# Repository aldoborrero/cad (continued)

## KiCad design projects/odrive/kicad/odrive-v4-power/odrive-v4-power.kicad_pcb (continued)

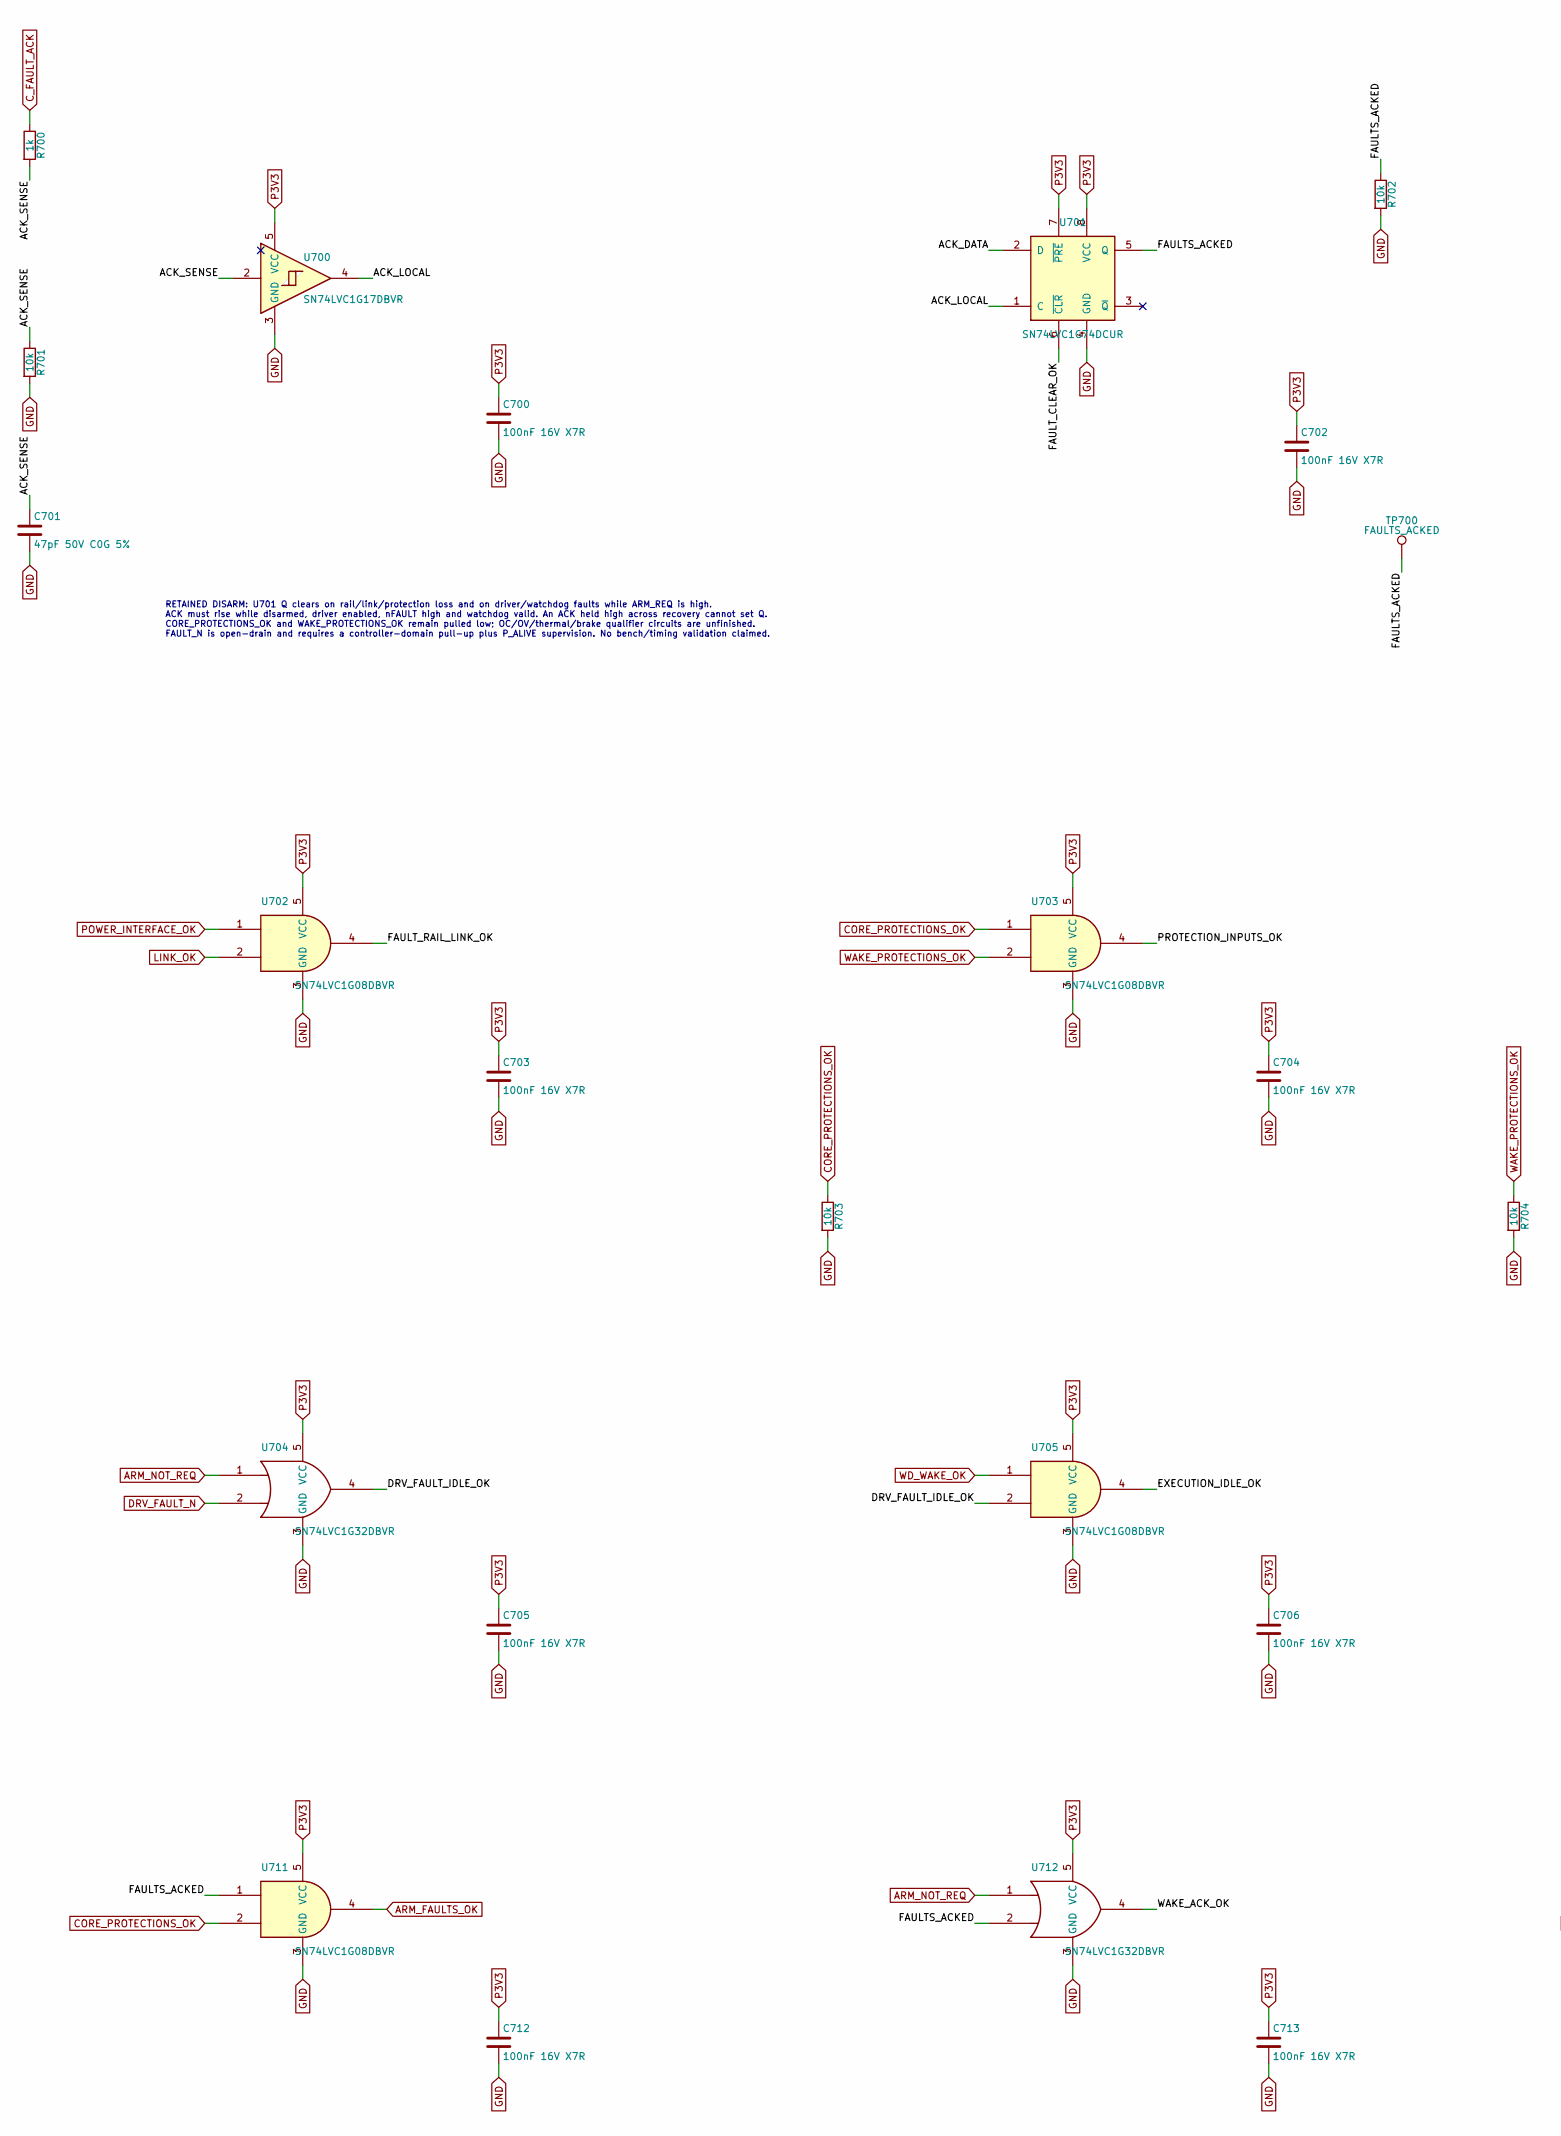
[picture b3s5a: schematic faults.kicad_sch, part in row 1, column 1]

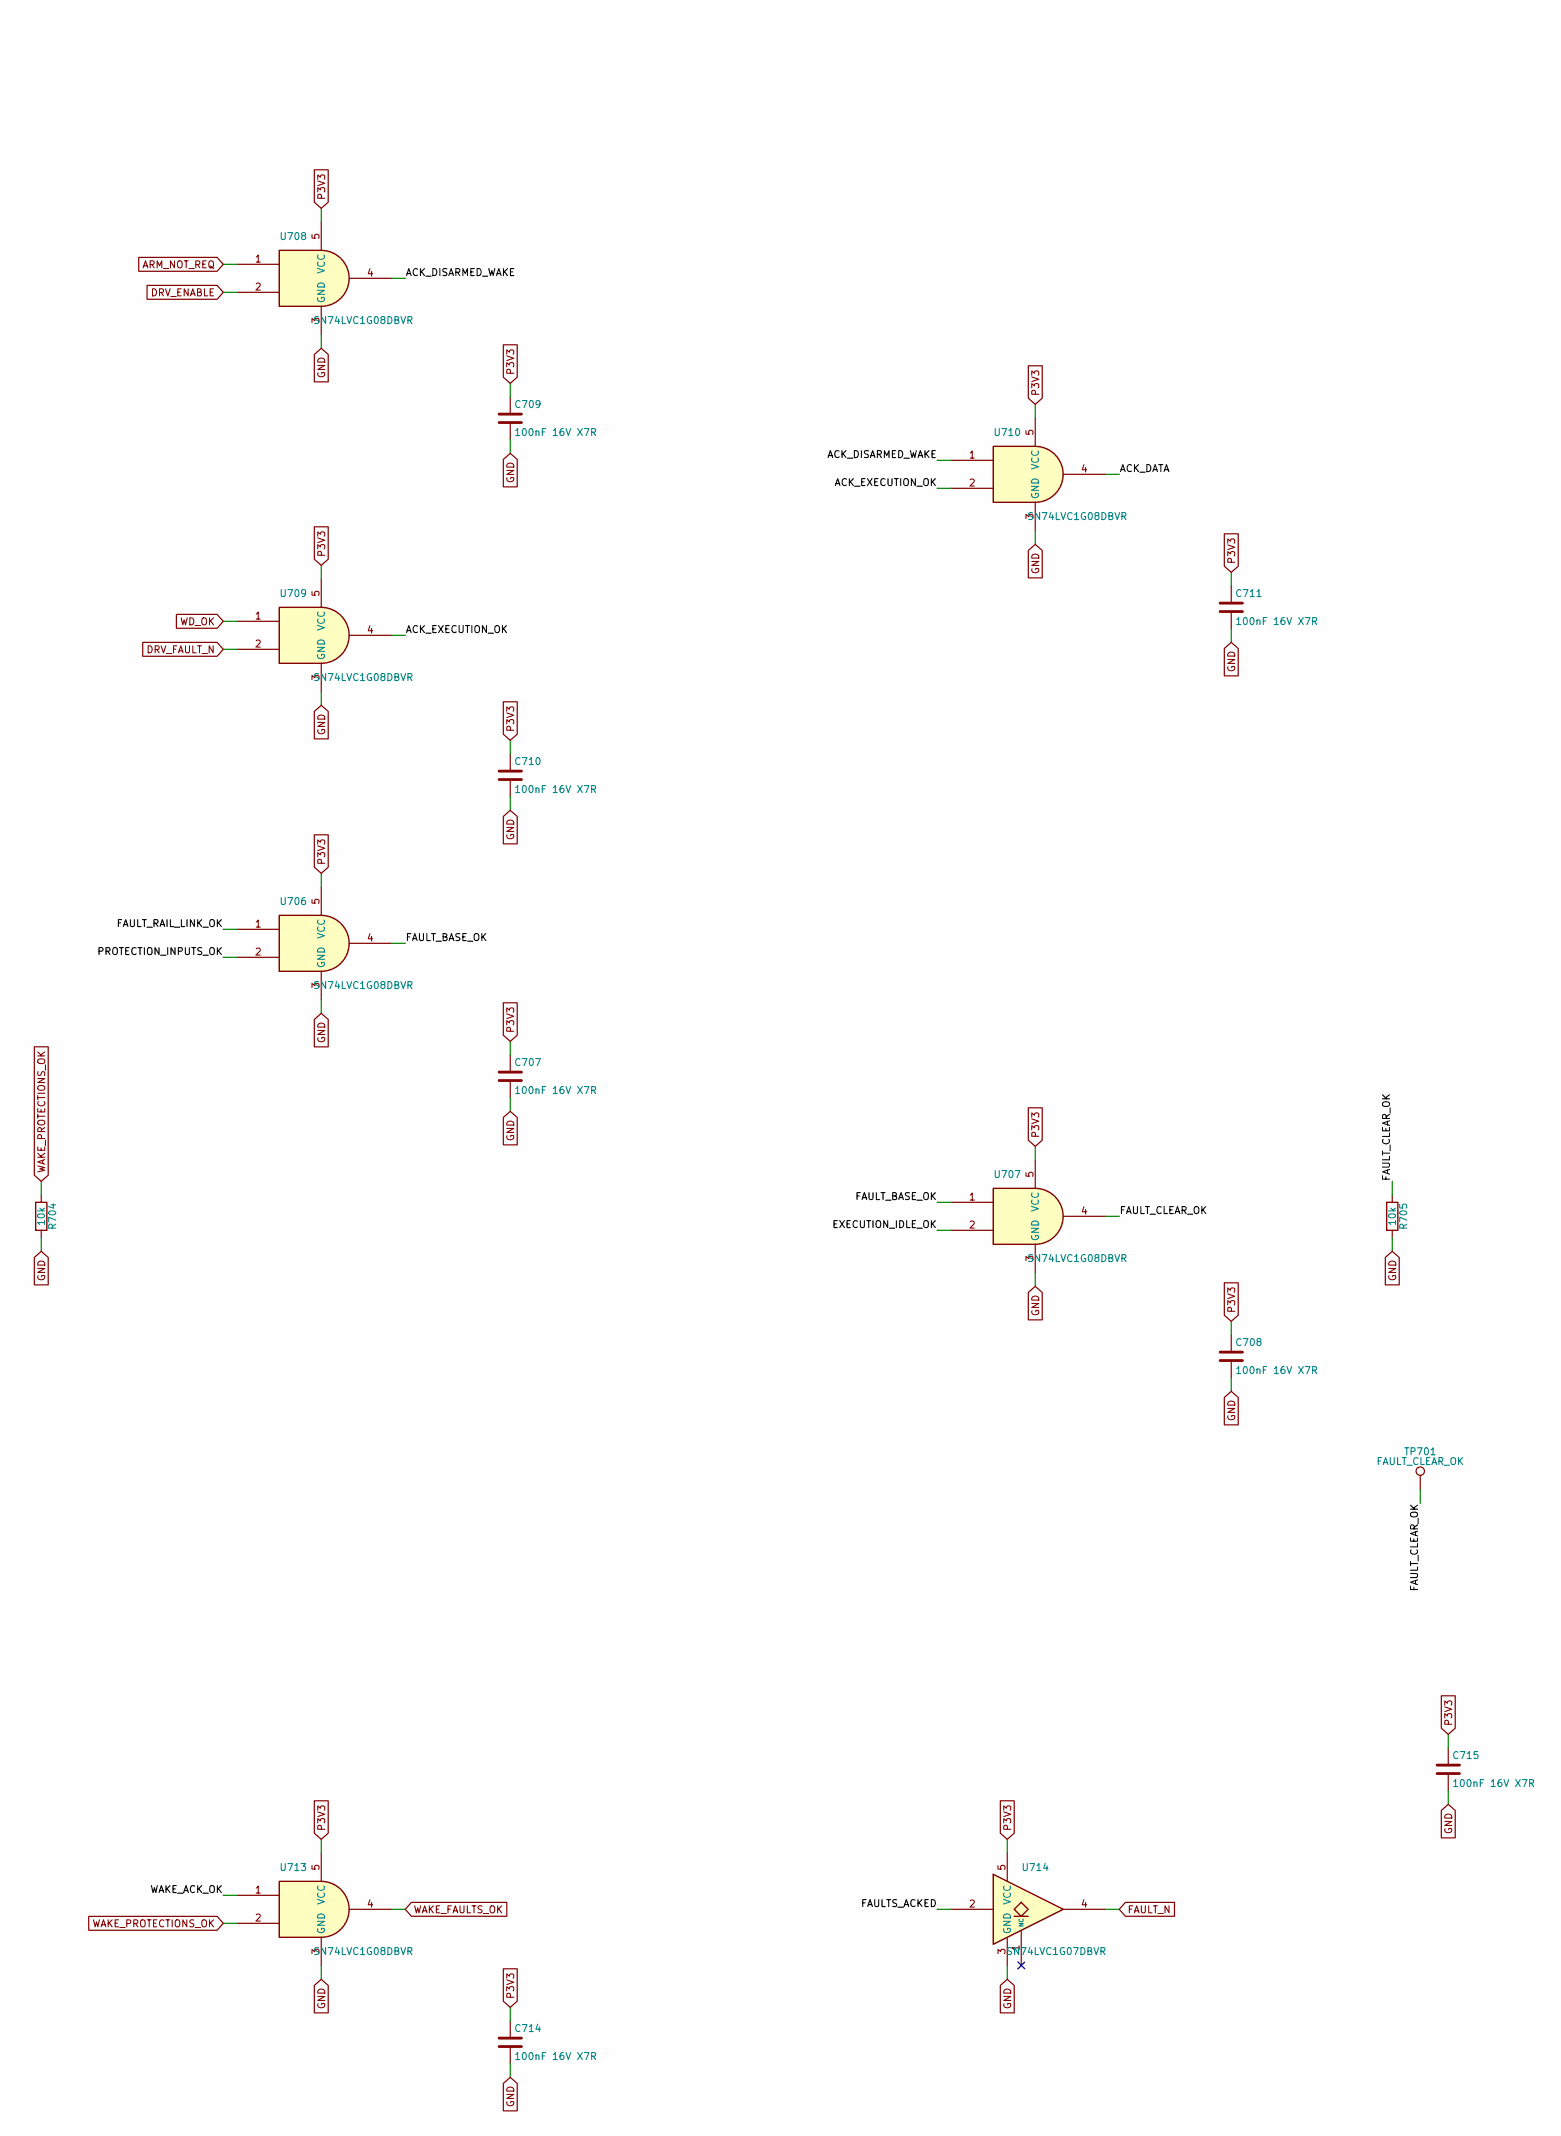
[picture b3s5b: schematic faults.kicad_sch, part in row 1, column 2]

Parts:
C700, C702, C703, C704, C705, C706, C707, C708, C709, C710, C711, C712, C713, C714, C715: 100nF 16V X7R; C_0603_1608Metric
C701: 47pF 50V C0G 5%; C_0603_1608Metric
R700: 1k; R_0603_1608Metric
R701, R702, R703, R704, R705: 10k; R_0603_1608Metric
TP700: FAULTS_ACKED; TestPoint_Pad_D1.0mm
TP701: FAULT_CLEAR_OK; TestPoint_Pad_D1.0mm
U700: SN74LVC1G17DBVR; SOT-23-5
U701: SN74LVC1G74DCUR; TI_DCU0008A
U702, U703, U705, U706, U707, U708, U709, U710, U711, U713: SN74LVC1G08DBVR; SOT-23-5
U704, U712: SN74LVC1G32DBVR; SOT-23-5
U714: SN74LVC1G07DBVR; SOT-23-5

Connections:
/Retained faults and acknowledgement/ACK_DATA: U701.2 (D), U710.4
/Retained faults and acknowledgement/ACK_DISARMED_WAKE: U708.4, U710.1
/Retained faults and acknowledgement/ACK_EXECUTION_OK: U709.4, U710.2
/Retained faults and acknowledgement/ACK_LOCAL: U700.4, U701.1 (C)
/Retained faults and acknowledgement/ACK_SENSE: C701.1, R700.2, R701.1, U700.2
/Retained faults and acknowledgement/DRV_FAULT_IDLE_OK: U704.4, U705.2
/Retained faults and acknowledgement/EXECUTION_IDLE_OK: U705.4, U707.2
/Retained faults and acknowledgement/FAULTS_ACKED: R702.1, TP700.1, U701.5 (Q), U711.1, U712.2, U714.2
/Retained faults and acknowledgement/FAULT_BASE_OK: U706.4, U707.1
/Retained faults and acknowledgement/FAULT_CLEAR_OK: R705.1, TP701.1, U701.6 (~CLR), U707.4
/Retained faults and acknowledgement/FAULT_RAIL_LINK_OK: U702.4, U706.1
/Retained faults and acknowledgement/PROTECTION_INPUTS_OK: U703.4, U706.2
/Retained faults and acknowledgement/WAKE_ACK_OK: U712.4, U713.1
ARM_FAULTS_OK: U711.4; also elsewhere on the board
ARM_NOT_REQ: U704.1, U708.1, U712.1; also elsewhere on the board
CORE_PROTECTIONS_OK: R703.1, U703.1, U711.2
C_FAULT_ACK: R700.1; also elsewhere on the board
DRV_ENABLE: U708.2; also elsewhere on the board
DRV_FAULT_N: U704.2, U709.2; also elsewhere on the board
FAULT_N: U714.4; also elsewhere on the board
GND: C700.2, C701.2, C702.2, C703.2, C704.2, C705.2, C706.2, C707.2, C708.2, C709.2, C710.2, C711.2, C712.2, C713.2, C714.2, C715.2, R701.2, R702.2, R703.2, R704.2, R705.2, U700.3 (GND), U701.4 (GND), U702.3 (GND), U703.3 (GND), U704.3 (GND), U705.3 (GND), U706.3 (GND), U707.3 (GND), U708.3 (GND), U709.3 (GND), U710.3 (GND), U711.3 (GND), U712.3 (GND), U713.3 (GND), U714.3 (GND); also elsewhere on the board
LINK_OK: U702.2; also elsewhere on the board
P3V3: C700.1, C702.1, C703.1, C704.1, C705.1, C706.1, C707.1, C708.1, C709.1, C710.1, C711.1, C712.1, C713.1, C714.1, C715.1, U700.5 (VCC), U701.7 (~PRE), U701.8 (VCC), U702.5 (VCC), U703.5 (VCC), U704.5 (VCC), U705.5 (VCC), U706.5 (VCC), U707.5 (VCC), U708.5 (VCC), U709.5 (VCC), U710.5 (VCC), U711.5 (VCC), U712.5 (VCC), U713.5 (VCC), U714.5 (VCC); also elsewhere on the board
POWER_INTERFACE_OK: U702.1; also elsewhere on the board
WAKE_FAULTS_OK: U713.4; also elsewhere on the board
WAKE_PROTECTIONS_OK: R704.1, U703.2, U713.2
WD_OK: U709.1; also elsewhere on the board
WD_WAKE_OK: U705.1; also elsewhere on the board

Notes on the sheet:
RETAINED DISARM: U701 Q clears on rail/link/protection loss and on driver/watchdog faults while ARM_REQ is high. ACK must rise while disarmed, driver enabled, nFAULT high and watchdog valid. An ACK held high across recovery cannot set Q. CORE_PROTECTIONS_OK and WAKE_PROTECTIONS_OK remain pulled low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

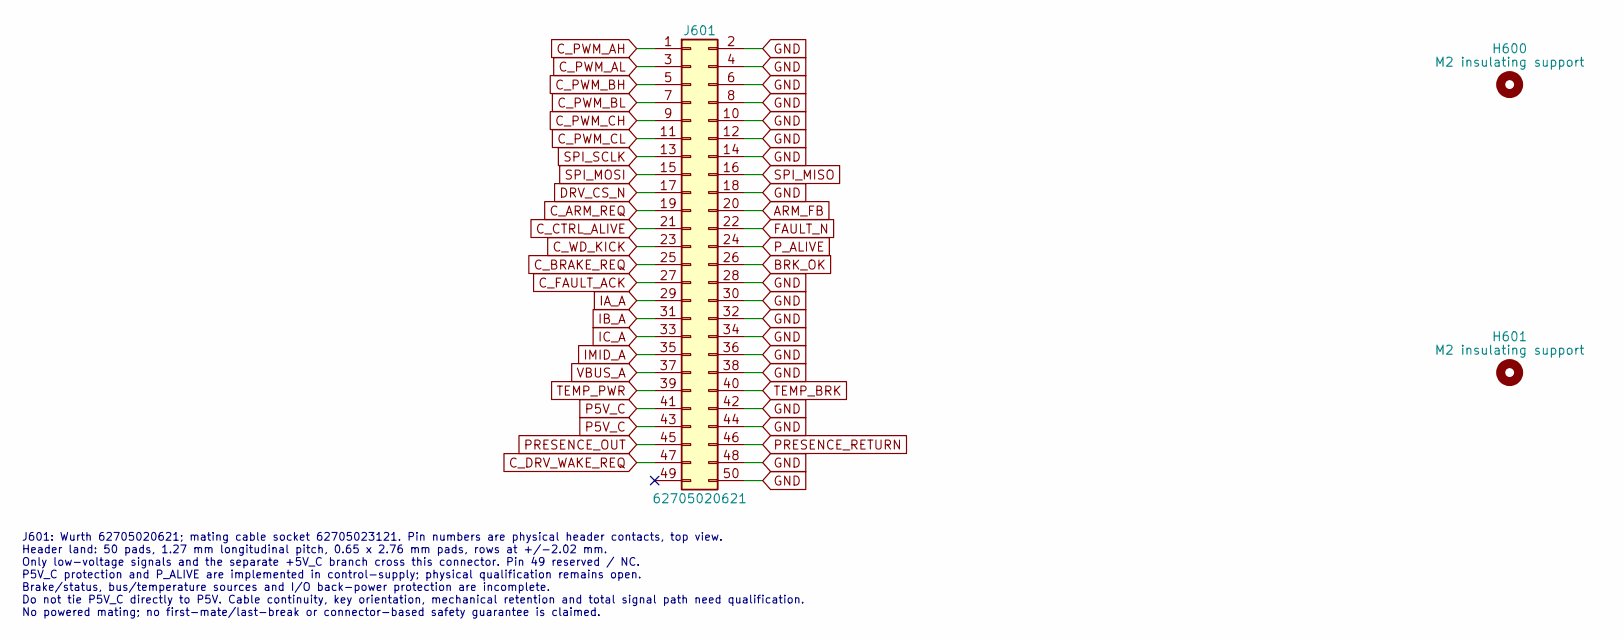
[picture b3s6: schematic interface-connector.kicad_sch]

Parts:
H600, H601: M2 insulating support; MountingHole_2.2mm_M2_Head5mm
J601: 62705020621; Wurth_62705020621_2x25_P1.27mm

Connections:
ARM_FB: J601.20; also elsewhere on the board
BRK_OK: J601.26
C_ARM_REQ: J601.19; also elsewhere on the board
C_BRAKE_REQ: J601.25
C_CTRL_ALIVE: J601.21; also elsewhere on the board
C_DRV_WAKE_REQ: J601.47; also elsewhere on the board
C_FAULT_ACK: J601.27; also elsewhere on the board
C_PWM_AH: J601.1; also elsewhere on the board
C_PWM_AL: J601.3; also elsewhere on the board
C_PWM_BH: J601.5; also elsewhere on the board
C_PWM_BL: J601.7; also elsewhere on the board
C_PWM_CH: J601.9; also elsewhere on the board
C_PWM_CL: J601.11; also elsewhere on the board
C_WD_KICK: J601.23; also elsewhere on the board
DRV_CS_N: J601.17; also elsewhere on the board
FAULT_N: J601.22; also elsewhere on the board
GND: J601.2, J601.4, J601.6, J601.8, J601.10, J601.12, J601.14, J601.18, J601.28, J601.30, J601.32, J601.34, J601.36, J601.38, J601.42, J601.44, J601.48, J601.50; also elsewhere on the board
IA_A: J601.29; also elsewhere on the board
IB_A: J601.31; also elsewhere on the board
IC_A: J601.33; also elsewhere on the board
IMID_A: J601.35; also elsewhere on the board
P5V_C: J601.41, J601.43; also elsewhere on the board
PRESENCE_OUT: J601.45; also elsewhere on the board
PRESENCE_RETURN: J601.46; also elsewhere on the board
P_ALIVE: J601.24; also elsewhere on the board
SPI_MISO: J601.16; also elsewhere on the board
SPI_MOSI: J601.15; also elsewhere on the board
SPI_SCLK: J601.13; also elsewhere on the board
TEMP_BRK: J601.40
TEMP_PWR: J601.39
VBUS_A: J601.37

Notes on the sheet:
J601: Wurth 62705020621; mating cable socket 62705023121. Pin numbers are physical header contacts, top view. Header land: 50 pads, 1.27 mm longitudinal pitch, 0.65 x 2.76 mm pads, rows at +/-2.02 mm. Only low-voltage signals and the separate +5V_C branch cross this connector. Pin 49 reserved / NC.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

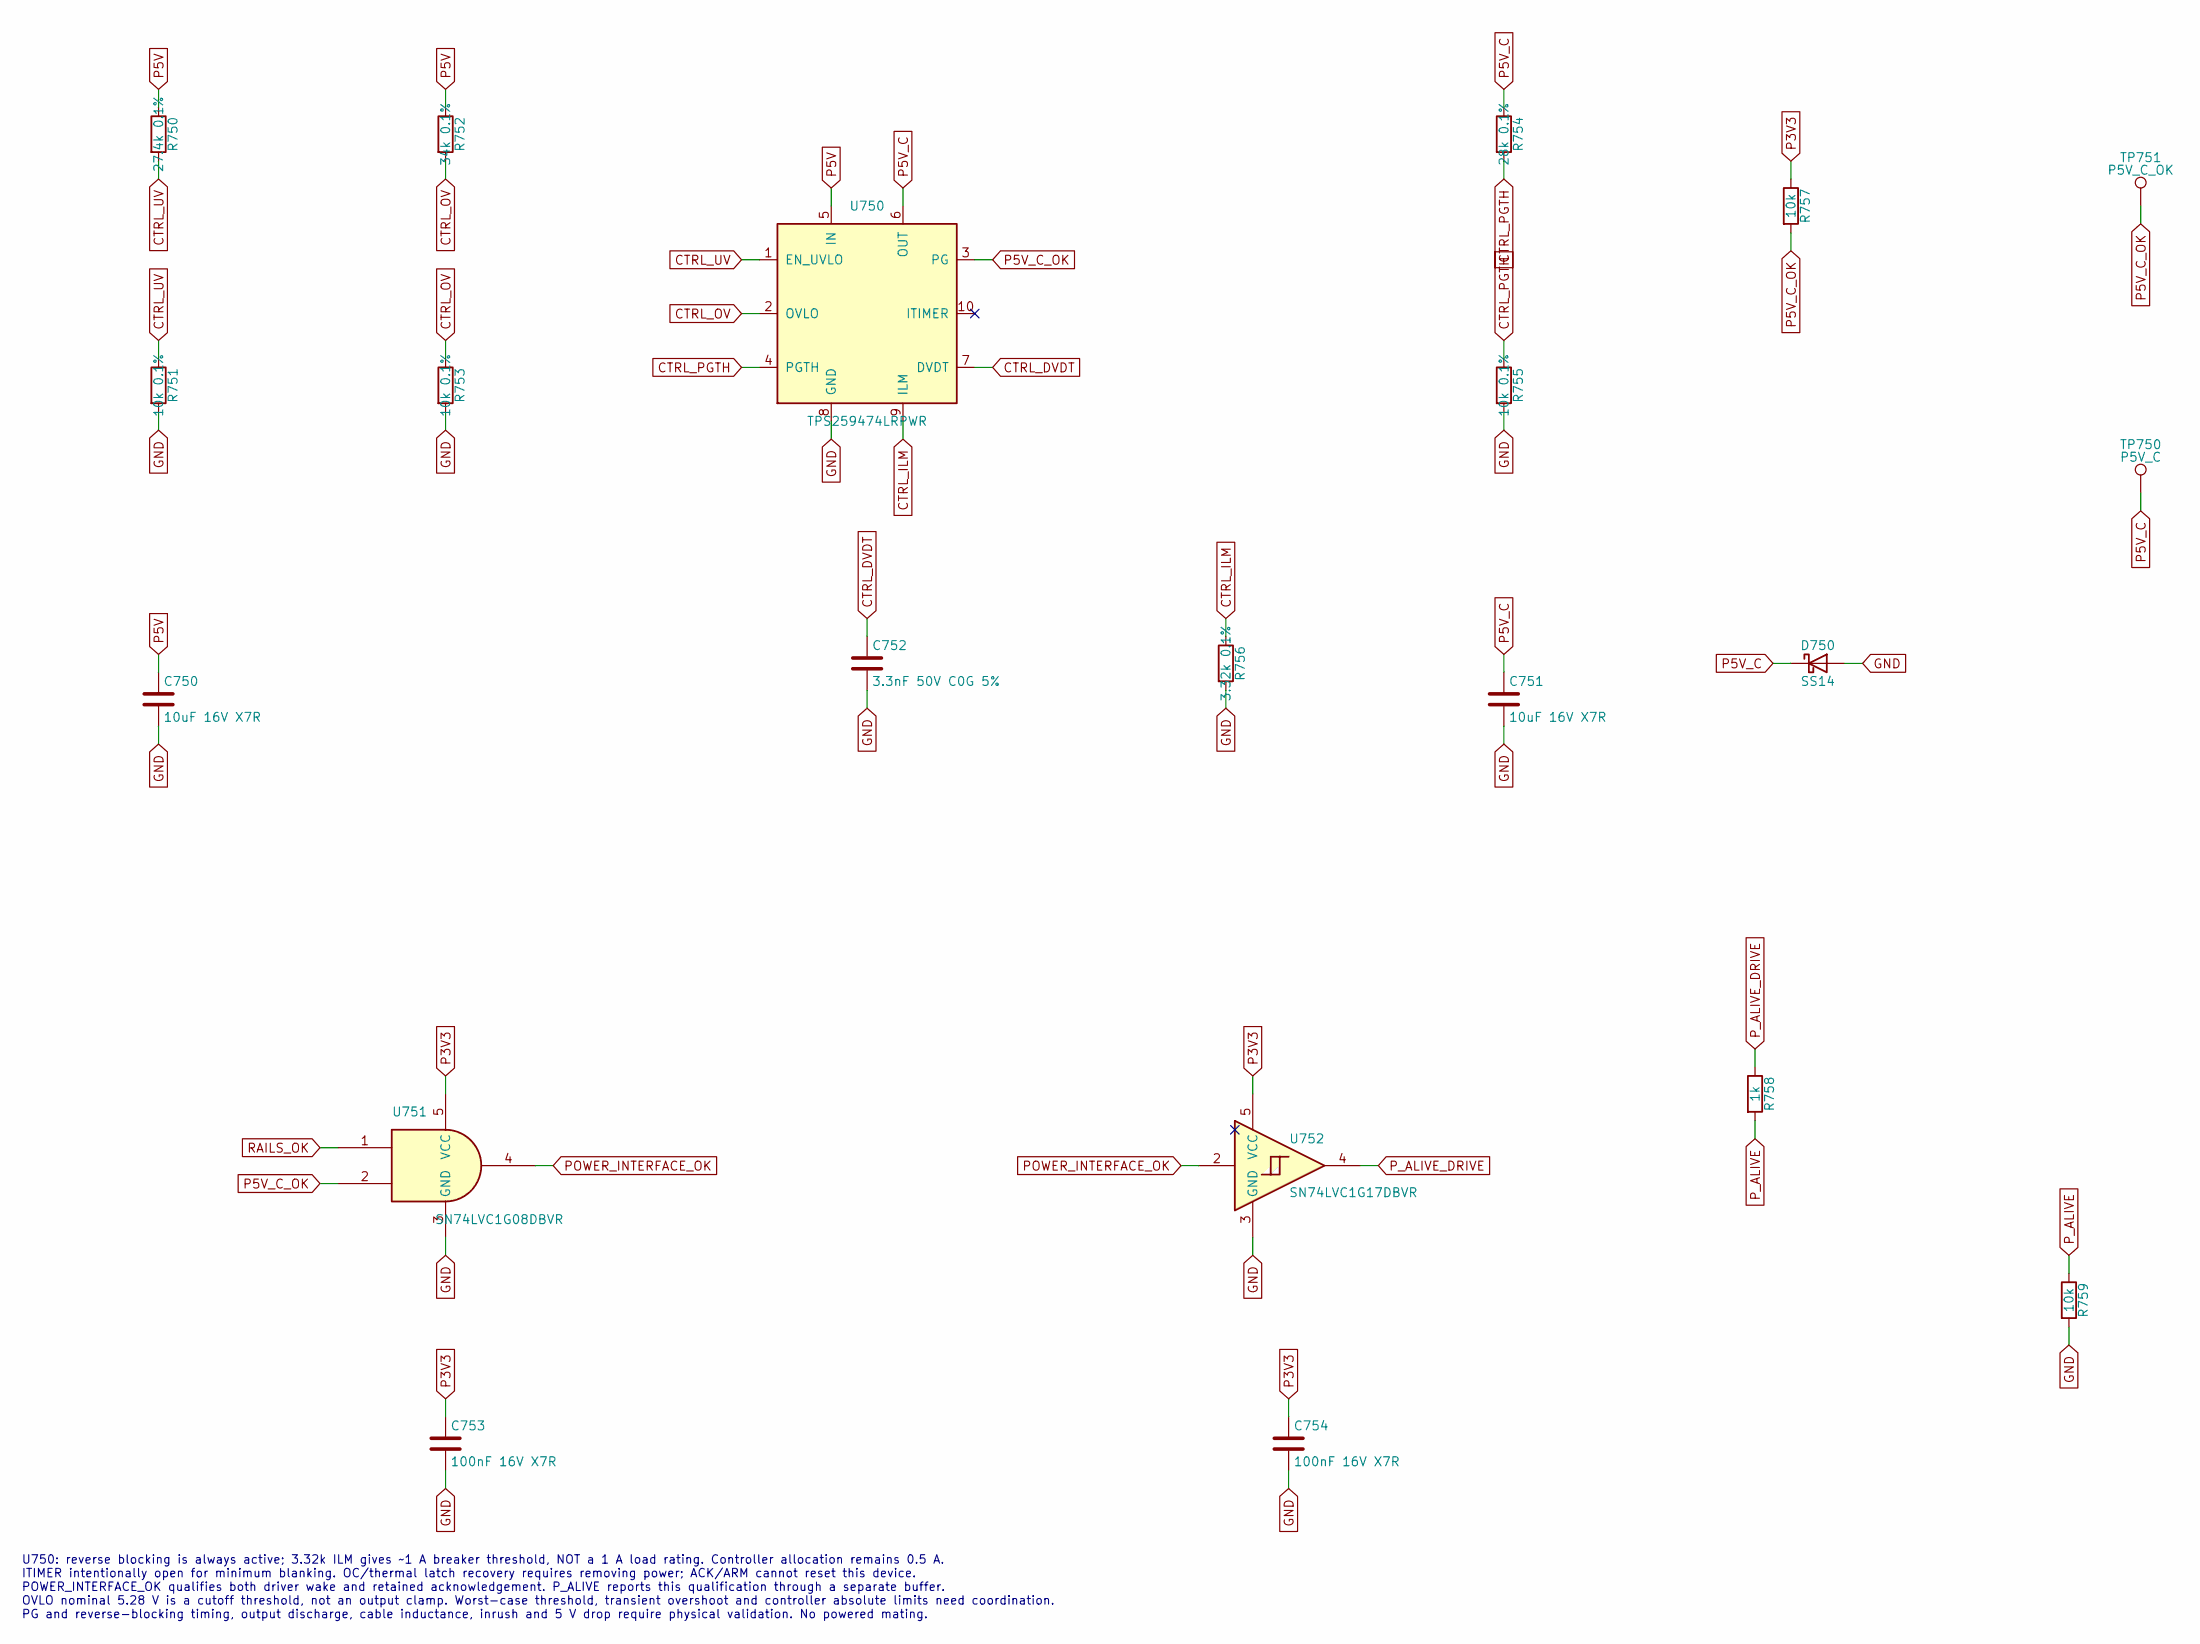
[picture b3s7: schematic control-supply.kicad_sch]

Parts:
C750, C751: 10uF 16V X7R; C_0805_2012Metric
C752: 3.3nF 50V C0G 5%; C_0603_1608Metric
C753, C754: 100nF 16V X7R; C_0603_1608Metric
D750: SS14; D_SMA
R750: 27.4k 0.1%; R_0603_1608Metric
R751, R753, R755: 10k 0.1%; R_0603_1608Metric
R752: 34k 0.1%; R_0603_1608Metric
R754: 28k 0.1%; R_0603_1608Metric
R756: 3.32k 0.1%; R_0603_1608Metric
R757, R759: 10k; R_0603_1608Metric
R758: 1k; R_0603_1608Metric
TP750: P5V_C; TestPoint_Pad_D1.0mm
TP751: P5V_C_OK; TestPoint_Pad_D1.0mm
U750: TPS259474LRPWR; TI_RPW0010A
U751: SN74LVC1G08DBVR; SOT-23-5
U752: SN74LVC1G17DBVR; SOT-23-5

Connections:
CTRL_DVDT: C752.1, U750.7 (DVDT)
CTRL_ILM: R756.1, U750.9 (ILM)
CTRL_OV: R752.2, R753.1, U750.2 (OVLO)
CTRL_PGTH: R754.2, R755.1, U750.4 (PGTH)
CTRL_UV: R750.2, R751.1, U750.1 (EN_UVLO)
GND: C750.2, C751.2, C752.2, C753.2, C754.2, D750.2 (A), R751.2, R753.2, R755.2, R756.2, R759.2, U750.8 (GND), U751.3 (GND), U752.3 (GND); also elsewhere on the board
P3V3: C753.1, C754.1, R757.1, U751.5 (VCC), U752.5 (VCC); also elsewhere on the board
P5V: C750.1, R750.1, R752.1, U750.5 (IN); also elsewhere on the board
P5V_C: C751.1, D750.1 (K), R754.1, TP750.1, U750.6 (OUT); also elsewhere on the board
P5V_C_OK: R757.2, TP751.1, U750.3 (PG), U751.2
POWER_INTERFACE_OK: U751.4, U752.2; also elsewhere on the board
P_ALIVE: R758.2, R759.1; also elsewhere on the board
P_ALIVE_DRIVE: R758.1, U752.4
RAILS_OK: U751.1; also elsewhere on the board

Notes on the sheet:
U750: reverse blocking is always active; 3.32k ILM gives ~1 A breaker threshold, NOT a 1 A load rating. Controller allocation remains 0.5 A. ITIMER intentionally open for minimum blanking. OC/thermal latch recovery requires removing power; ACK/ARM cannot reset this device. POWER_INTERFACE_OK qualif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

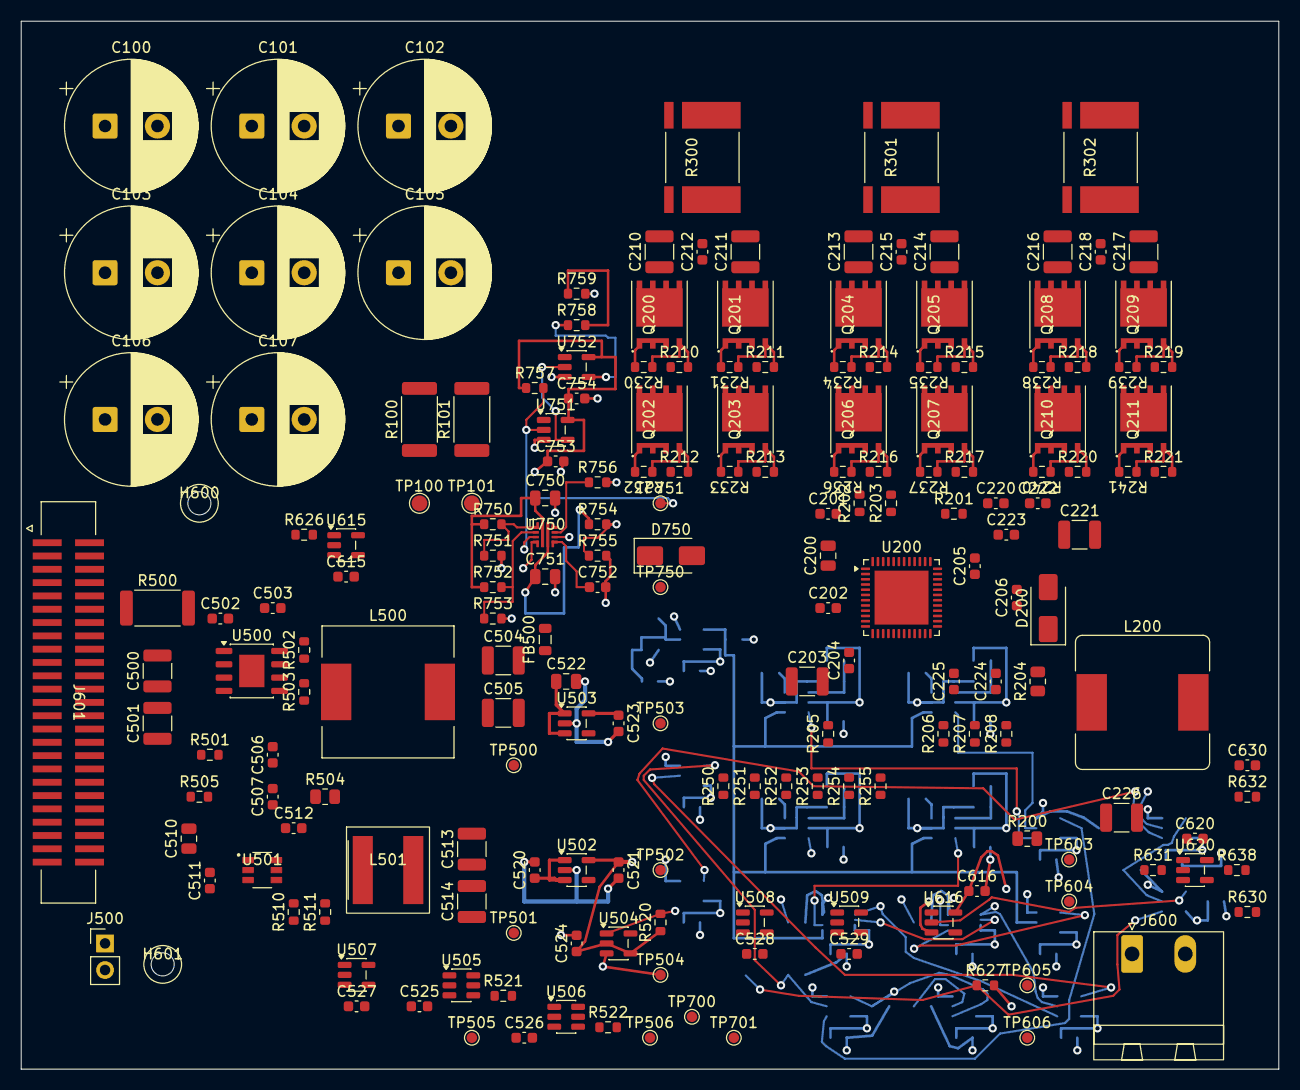
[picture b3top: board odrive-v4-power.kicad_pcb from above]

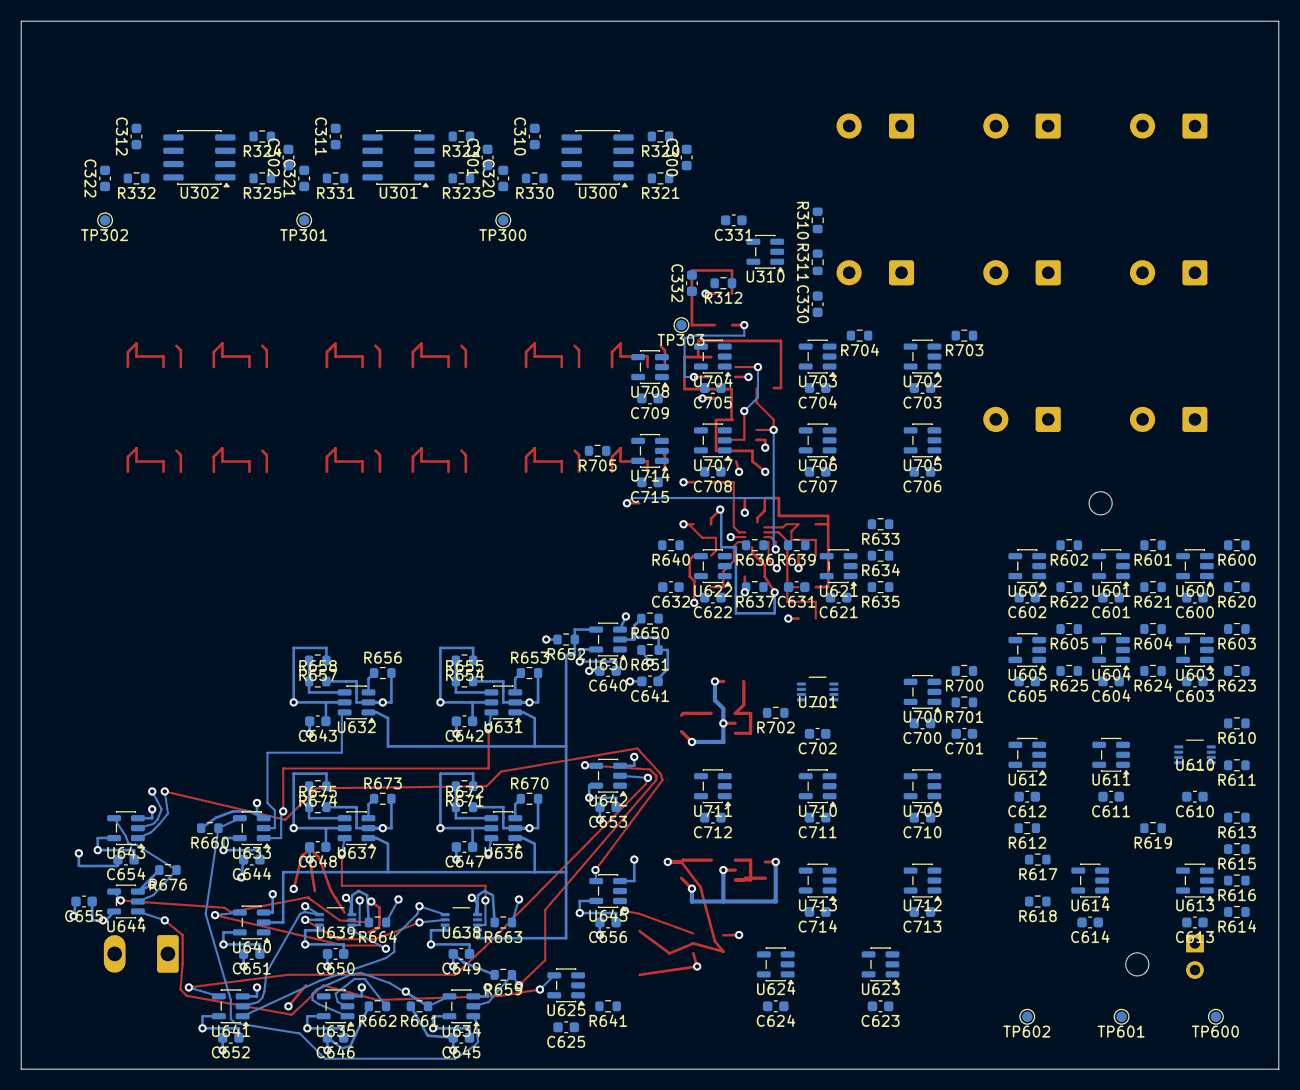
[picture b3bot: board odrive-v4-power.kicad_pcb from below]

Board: 4 copper layers, 120.0 x 100.0 mm, 382 parts (191 on the bottom side), 183 nets.

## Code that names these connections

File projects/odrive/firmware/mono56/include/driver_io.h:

#pragma once
#include <stdbool.h>
#include <stdint.h>
#ifdef __cplusplus
extern "C" {
#endif

// EXTI pending bits retained until explicit session teardown. Falling edges:
// PD2 nFAULT, PC6 actual ENABLE, PC7 brake permission.
#define MONO56_DRIVER_FAULT_EDGE (1u << 2)
#define MONO56_DRIVER_ENABLE_EDGE (1u << 6)
#define MONO56_DRIVER_BRAKE_EDGE (1u << 7)

typedef struct {
    bool valid, quiet, requested, enable_feedback, brake_ok, nfault_high;
    uint32_t falling_edges;
    // Six GPIO PWM inputs LOW and CCER/MOE/AOE clear, independently of CEN/DIER.
    // Allows internal timer/ADC operation, never physical PWM switching.
    bool pwm_inhibited;
} mono56_driver_inputs;

// Exclusive TIM1, PA8..10, PB12..15, PC6/7, PD2 and EXTI2/6/7 owner.
// The previous PWM/DMA owner must already be stopped. Never call on a running
// controller. Inhibits first, holds six PWM GPIOs LOW, configures feedback without
// pulls and falling-edge capture. Does not enable NVIC interrupts or the driver.
// EXTI IMR is armed, but NVIC EXTI2 and EXTI9_5 must remain disabled; this
// polled startup owner cannot share those vectors with active IRQ users.
// Active foreign EXTI ownership is rejected. False still inhibits the motor.
bool mono56_driver_io_prepare(void);
mono56_driver_inputs mono56_driver_io_read(void);
// Caller must FIRST establish full driver sleep, fresh bus permission and the
// qualified startup sequence. Atomic local checks do not establish those facts.
// bus_permitted is checked with IRQs masked immediately before local input checks;
// it must be nonblocking and validate freshness/retained bus faults without IRQs.
// This can raise PB12 once; duplicate requests fail and inhibit. Never starts PWM.
bool mono56_driver_io_request_enable(bool (*bus_permitted)(void *), void *context);
// After the qualified wake interval, establish nFAULT edge history. Initial
// wake UV faults may have asserted nFAULT. Clears ONLY PD2's prior pending bit,
// then requires live healthy feedback with no new pending fault. Call once per
// session; repeated calls fail/inhibit so they cannot erase a later fault.
bool mono56_driver_io_qualify_nfault(void);
// Inhibit and release owned EXTI detection. Leaves motor GPIOs LOW. This is the
// explicit teardown; read/request cannot recover a failed request implicitly.
void mono56_driver_io_shutdown(void);
#ifdef __cplusplus
}
#endif
